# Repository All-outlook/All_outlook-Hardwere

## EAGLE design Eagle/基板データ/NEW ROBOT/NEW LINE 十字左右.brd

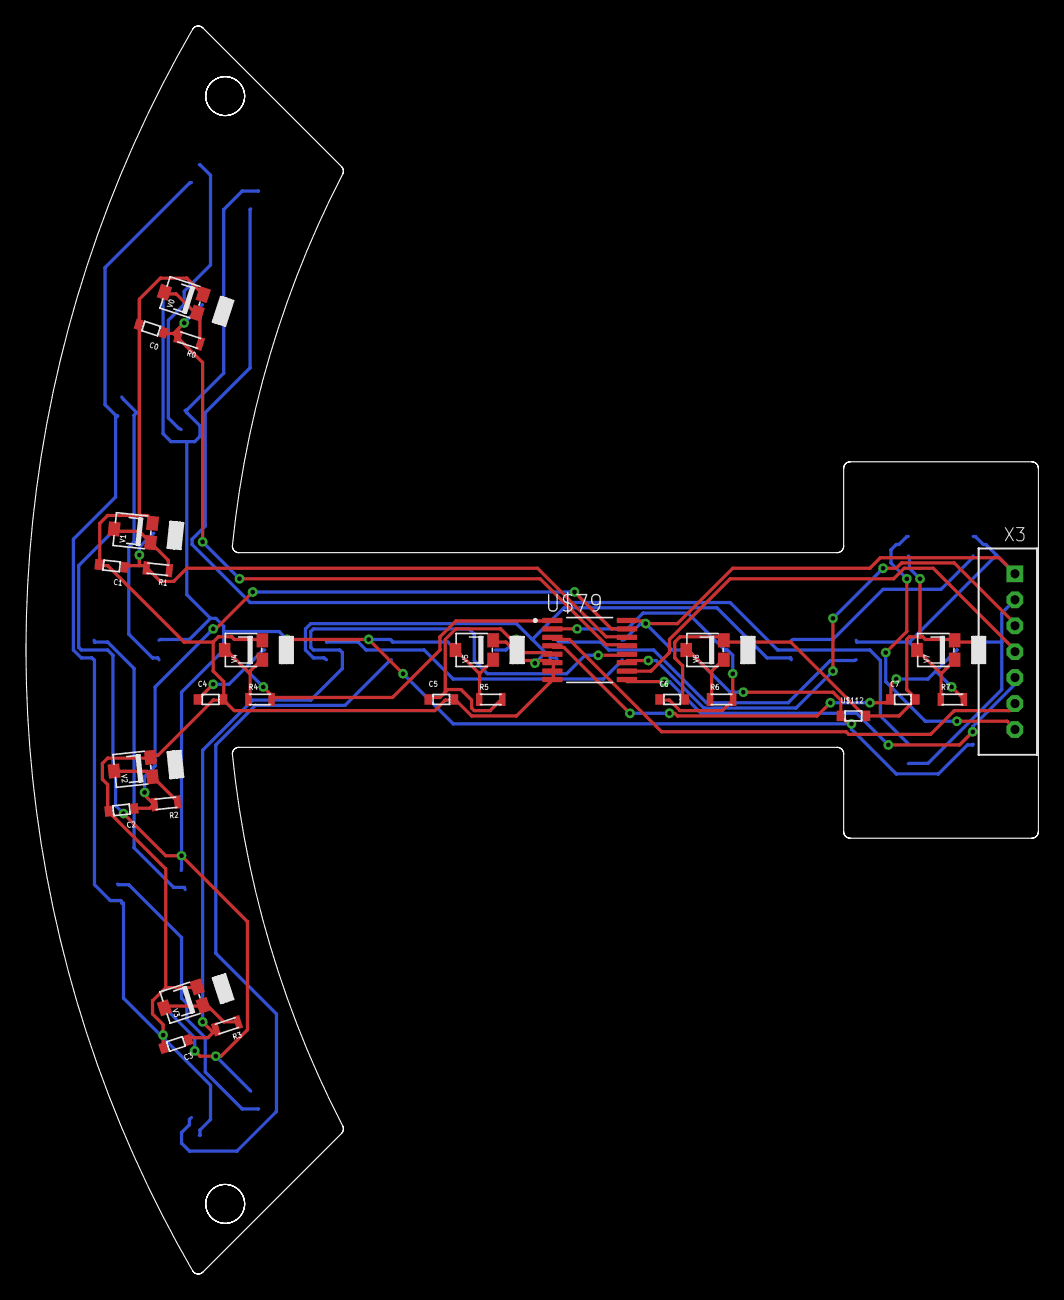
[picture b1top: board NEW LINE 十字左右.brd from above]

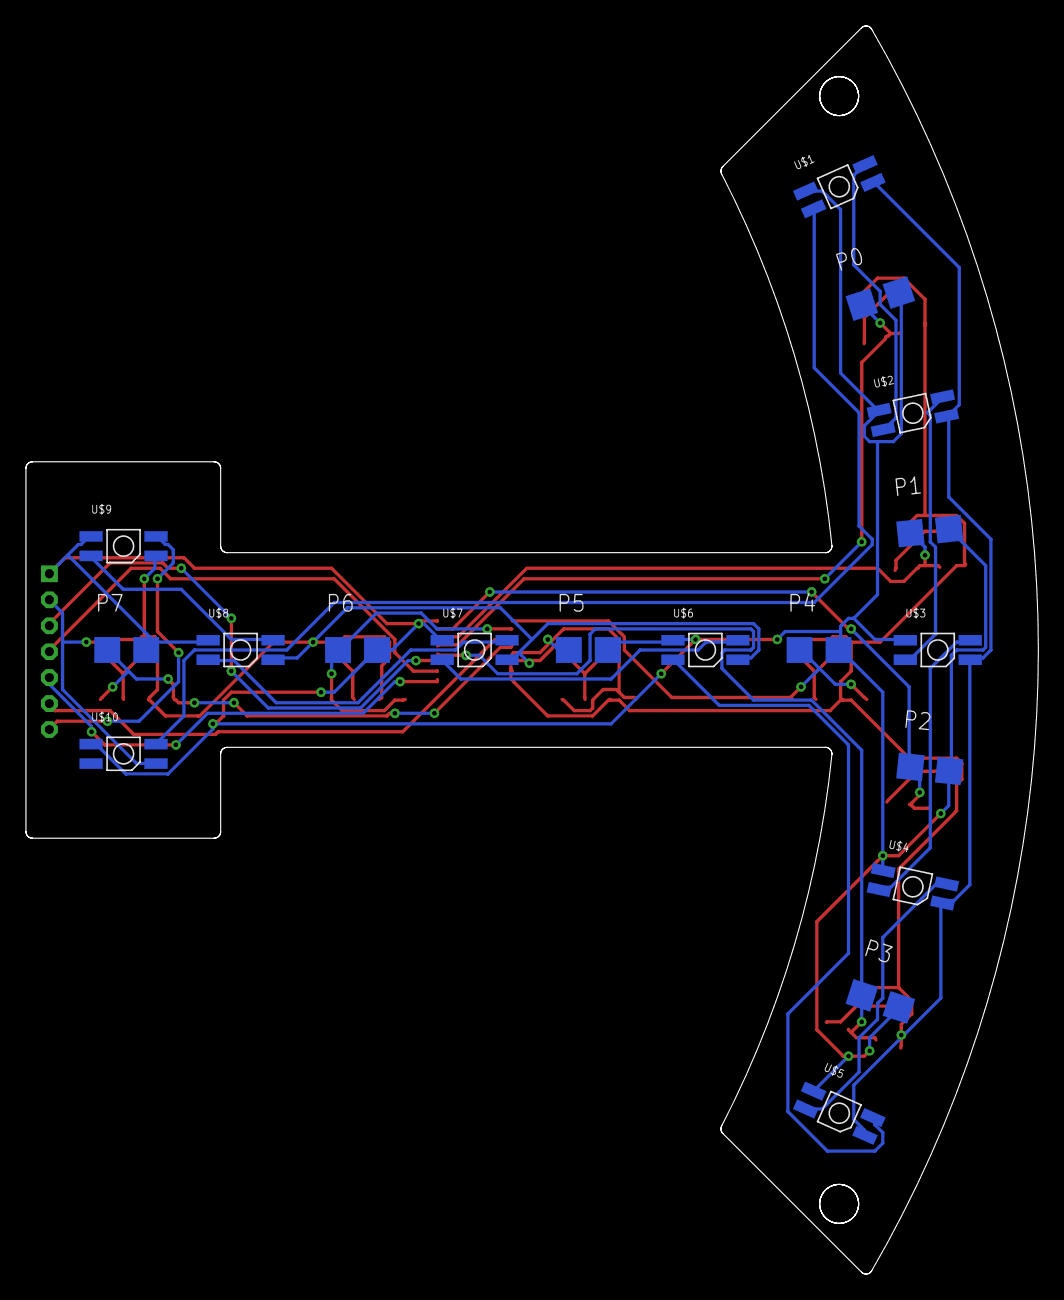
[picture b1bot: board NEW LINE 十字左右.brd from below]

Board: 2 copper layers, 78.0 x 96.2 mm, 45 parts (10 on the bottom side), 32 nets.

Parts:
C0, C1, C2, C3, C4, C5, C6, C7: 1608; CON
P0, P1, P2, P3, P4, P5, P6, P7: PHOTO
R0, R1, R2, R3, R4, R5, R6, R7: R; 1608
U$1, U$2, U$3, U$4, U$5, U$6, U$7, U$8, U$9, U$10: LED
U$79: AM; SOP65P640X120-16N
U$112: 1608; CON
V0, V1, V2, V3, V4, V5, V6, V7: VR
X3: B7B-PH-K-S

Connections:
+5V: P0.P$1, P1.P$1, P2.P$1, P3.P$1, P4.P$1, P5.P$1, P6.P$1, P7.P$1, U$1.P$1, U$2.P$1, U$3.P$1, U$4.P$1, U$5.P$1, U$6.P$1, U$7.P$1, U$8.P$1, U$9.P$1, U$10.P$1, U$79.16, U$112.P$1, X3.1
A: U$79.11, X3.3
B: U$79.10, X3.4
C: U$79.9, X3.5
CH0: C0.P$1, P0.P$2, R0.P$2, U$79.13
CH1: C1.P$1, P1.P$2, R1.P$2, U$79.14
CH2: C2.P$1, P2.P$2, R2.P$2, U$79.15
CH3: C3.P$1, P3.P$2, R3.P$2, U$79.12
CH4: C4.P$1, P4.P$2, R4.P$2, U$79.1
CH5: C5.P$1, P5.P$2, R5.P$2, U$79.5
CH6: C6.P$1, P6.P$2, R6.P$2, U$79.2
CH7: C7.P$1, P7.P$2, R7.P$2, U$79.4
COM: U$79.3, X3.6
FLED: U$9.P$4, X3.7
GND1: C0.P$2, C1.P$2, C2.P$2, C3.P$2, C4.P$2, C5.P$2, C6.P$2, C7.P$2, U$1.P$3, U$2.P$3, U$3.P$3, U$4.P$3, U$5.P$3, U$6.P$3, U$7.P$3, U$8.P$3, U$9.P$3, U$10.P$3, U$79.6, U$79.7, U$79.8, U$112.P$2, V0.P$3, V1.P$3, V2.P$3, V3.P$3, V4.P$3, V5.P$3, V6.P$3, V7.P$3, X3.2
unnamed: U$1.P$2, U$10.P$4
unnamed: U$1.P$4, U$2.P$2
unnamed: U$2.P$4, U$3.P$2
unnamed: U$3.P$4, U$4.P$2
unnamed: U$4.P$4, U$5.P$2
unnamed: U$5.P$4, U$6.P$2
unnamed: U$6.P$4, U$7.P$2
unnamed: U$7.P$4, U$8.P$2
unnamed: U$8.P$4, U$9.P$2
unnamed: R0.P$1, V0.P$1, V0.P$2
unnamed: R1.P$1, V1.P$1, V1.P$2
unnamed: R2.P$1, V2.P$1, V2.P$2
unnamed: R3.P$1, V3.P$1, V3.P$2
unnamed: R4.P$1, V4.P$1, V4.P$2
unnamed: R5.P$1, V5.P$1, V5.P$2
unnamed: R6.P$1, V6.P$1, V6.P$2
unnamed: R7.P$1, V7.P$1, V7.P$2

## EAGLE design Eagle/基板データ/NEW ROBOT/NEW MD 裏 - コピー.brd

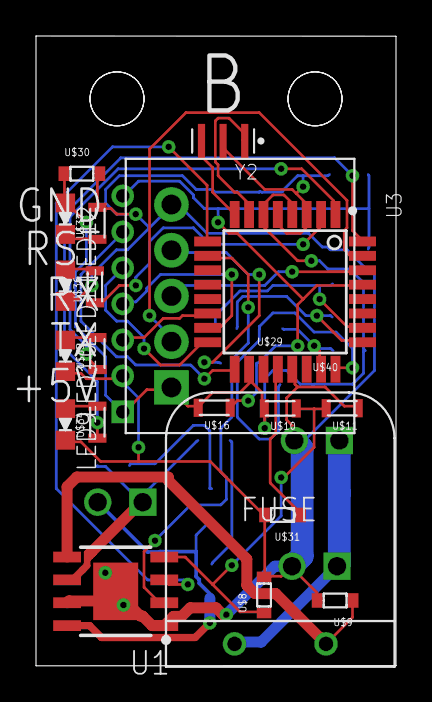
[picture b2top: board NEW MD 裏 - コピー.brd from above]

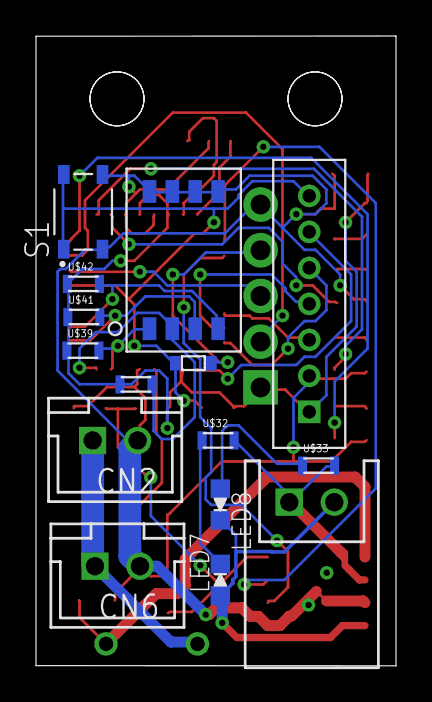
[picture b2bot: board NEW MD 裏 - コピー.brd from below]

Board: 2 copper layers, 20.0 x 35.0 mm, 35 parts (15 on the bottom side), 33 nets.

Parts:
CN2, CN6: B2B-XH-A
CN5: S2B-XH-A
LED7, LED8, LED9, LED10, LED11, LED12: LED1608
S1: SKRPACE010; SW_SKRPACE010
U1: L5973D; SOIC127P600X170-9N
U3: ATMEGA328P-AU; QFP80P900X900X120-32N
U$1: FUSE3.7A
U$8, U$9, U$29, U$30, U$31: 1608; CON
U$10, U$11, U$16, U$32, U$33, U$34, U$35, U$36, U$37, U$39, U$40, U$41, U$42: R; 1608
U$38: 4P
U$43: SPI
U$44: SI
Y2: CSTCE16M0V53-R0; OSC_CSTCE16M0V53-R0

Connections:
+5V: LED12.A, U3.4, U3.6, U3.18, U$10.P$2, U$16.P$2, U$30.P$1, U$39.P$1, U$40.P$1, U$41.P$1, U$42.P$1, U$43.P$1, U$44.P$1
A0: U3.23, U$38.1.1, U$39.P$2
A1: U3.24, U$38.2.1, U$40.P$2
A2: U3.25, U$38.3.1, U$41.P$2
A3: U3.26, U$38.4.1, U$42.P$2
D2: U3.32, U$34.P$1
D3: U3.1, U$35.P$1
D4: U3.2, U$36.P$1
GND: CN2.2, CN6.2, LED9.K, LED10.K, LED11.K, S1.3, S1.4, U1.1, U1.7, U1.9, U3.3, U3.5, U3.21, U$8.P$2, U$9.P$2, U$11.P$1, U$30.P$2, U$31.P$2, U$37.P$2, U$38.1.2, U$38.2.2, U$38.3.2, U$38.4.2, U$43.P$2, U$44.P$5, Y2.2
MISO: U3.16, U$43.P$5
MOSI: U3.15, U$43.P$4
unnamed: U1.5, U$1.P$2, U$9.P$1
unnamed: U1.4, U$8.P$1, U$10.P$1, U$11.P$2
unnamed: U3.20, U$31.P$1
unnamed: U$29.P$2, U$44.P$4
unnamed: U3.31, U$44.P$2
unnamed: U3.30, U$44.P$3
unnamed: CN2.1, CN6.1, U$1.P$1
unnamed: CN5.2, LED7.A, LED8.K, U1.8
unnamed: CN5.1, U1.6, U$32.P$2, U$33.P$2
unnamed: U1.2, U3.10
unnamed: U1.3, U3.9
unnamed: U3.7, Y2.1
unnamed: U3.8, Y2.3
unnamed: LED8.A, U$33.P$1
unnamed: LED7.K, U$32.P$1
unnamed: LED10.A, U$35.P$2
unnamed: LED9.A, U$34.P$2
unnamed: LED11.A, U$36.P$2
unnamed: LED12.K, U$37.P$1
RES: S1.1, S1.2, U3.29, U$16.P$1, U$29.P$1, U$43.P$7
SCK: U3.17, U$43.P$6
SS: U3.14, U$43.P$3

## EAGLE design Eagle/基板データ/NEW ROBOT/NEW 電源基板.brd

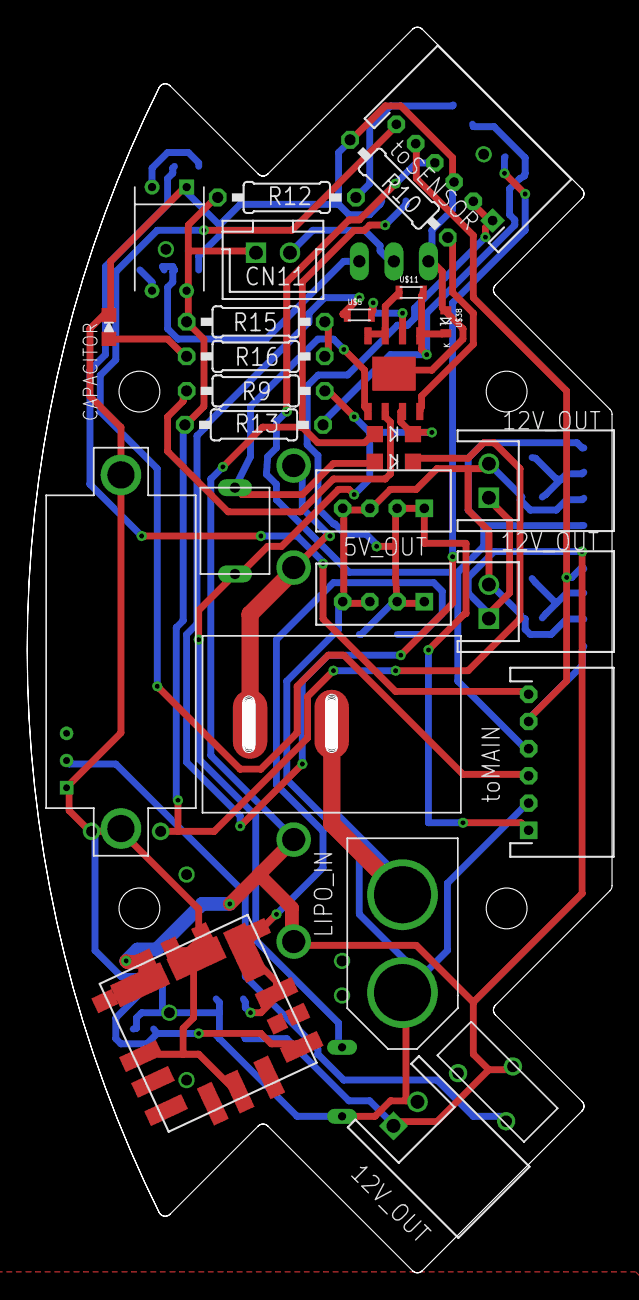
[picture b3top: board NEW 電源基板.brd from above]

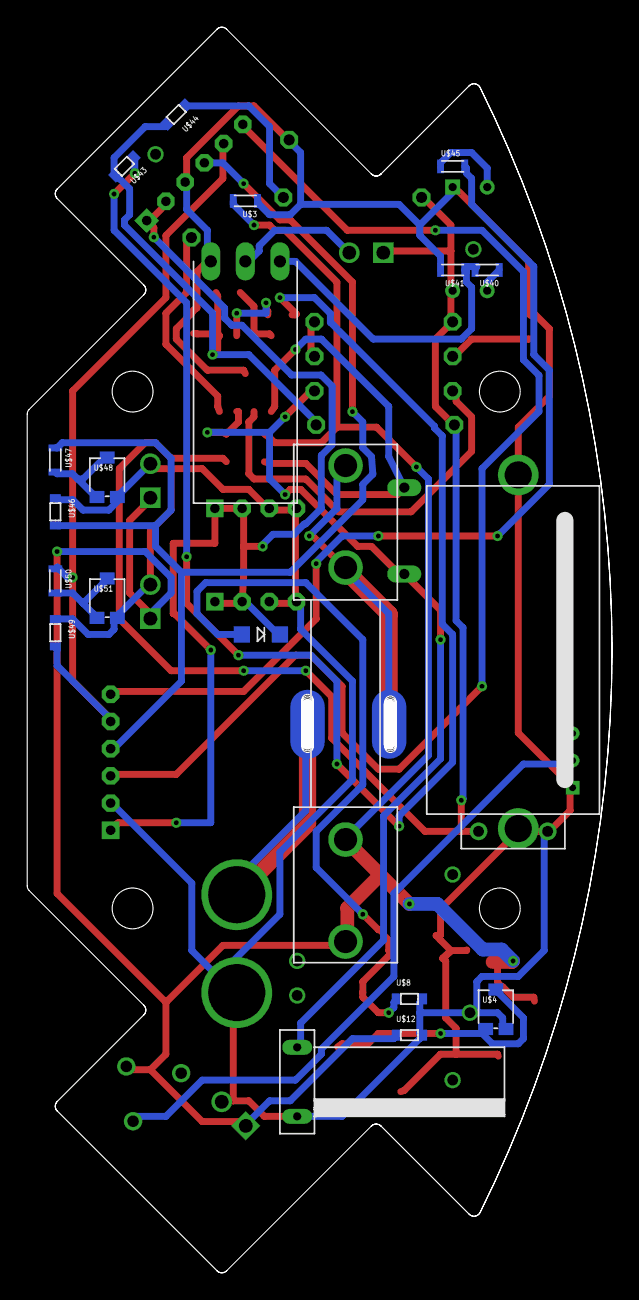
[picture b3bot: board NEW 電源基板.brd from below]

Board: 2 copper layers, 43.0 x 91.6 mm, 48 parts (20 on the bottom side), 30 nets.

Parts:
CAPACITOR: LED1608
CN5, CN6, CN7: S2B-XH-A
CN11: B2B-XH-A
FUES1: FUSE
R9, R10, R12, R13, R15, R16: 0207/10
U1: L5973D; HSOP8
U$1: SW3
U$2: DCDC; DC-DC
U$3, U$5, U$11, U$40, U$41, U$45, U$47, U$50: R; 1608
U$4, U$48, U$51: VR
U$6: V
U$7: XT60
U$8, U$12, U$43, U$44, U$46, U$49: 1608; CON
U$9: SSW
U$10, U$32, U$33: D
U$13: I
U$36: MOS
U$37: PHOTOCOUPLER
U$38: TD
U$39: FGFG2; FG2
U$42: 10
X1, X2: B4B-PH-K-S
X5, X6: S6B-PH-K-S

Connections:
+5V: U$10.P$2, X1.1, X1.2, X2.1, X2.2, X5.1, X5.2, X6.1
+12V: CN5.1, CN6.1, CN7.1, FUES1.P$1, FUES1.P$2, U$2.P$9, U$2.P$14, U$2.P$15, U$3.P$2, U$9.P$3, U$12.P$1, U$32.P$1
B1: U$46.P$2, U$47.P$1, X5.4, X6.4
B2: U$49.P$2, U$50.P$1, X5.5, X6.5
FLED: X5.6, X6.3
GND: CAPACITOR.K, CN5.2, CN6.2, CN7.2, R10.1, U1.9, U$2.P$1, U$2.P$5, U$2.P$10, U$2.P$16, U$2.P$17, U$3.P$1, U$4.P$3, U$6.P$1, U$6.P$4, U$6.P$5, U$7.P$2, U$8.P$2, U$12.P$2, U$36.P$3, U$37.P$1, U$38.P$1, U$39.P$2, U$41.P$2, U$42.P$2, U$46.P$1, U$48.P$3, U$49.P$1, U$51.P$3, X1.3, X1.4, X2.3, X2.4, X5.3, X6.2
K: U$45.P$2, X6.6
unnamed: U$6.P$2, U$9.P$1
unnamed: U$2.P$7, U$4.P$1, U$4.P$2
unnamed: U$2.P$8, U$2.P$11, U$2.P$18, U$8.P$1, U$10.P$1
unnamed: FUES1.P$3, FUES1.P$4, U$1.P$2, U$1.P$4
unnamed: U$1.P$1, U$1.P$3, U$7.P$1
unnamed: CN11.1, R12.1, R13.1, R15.1, U$33.P$2, U$37.P$4, U$39.P$1
unnamed: U$37.P$3, U$40.P$1
unnamed: CN11.2, U$36.P$2
unnamed: U$36.P$1, U$40.P$2, U$41.P$1
unnamed: R9.2, U1.3, U$13.P$1, U$32.P$2, U$42.P$1
unnamed: R9.1, U1.2
unnamed: R10.2, U1.4
unnamed: R13.2, U1.5, U$11.P$2, U$38.P$2, U$43.P$2, U$44.P$2
unnamed: R12.2, U$44.P$1
unnamed: U1.6, U$5.P$2
unnamed: U$5.P$1, U$43.P$1
unnamed: U$37.P$2, U$45.P$1
unnamed: U$47.P$2, U$48.P$1, U$48.P$2
unnamed: U$50.P$2, U$51.P$1, U$51.P$2
unnamed: R15.2, R16.1
unnamed: CAPACITOR.A, R16.2
PGND: U1.7, U1.8, U$11.P$1
SW: U1.1, U$13.P$2, U$33.P$1

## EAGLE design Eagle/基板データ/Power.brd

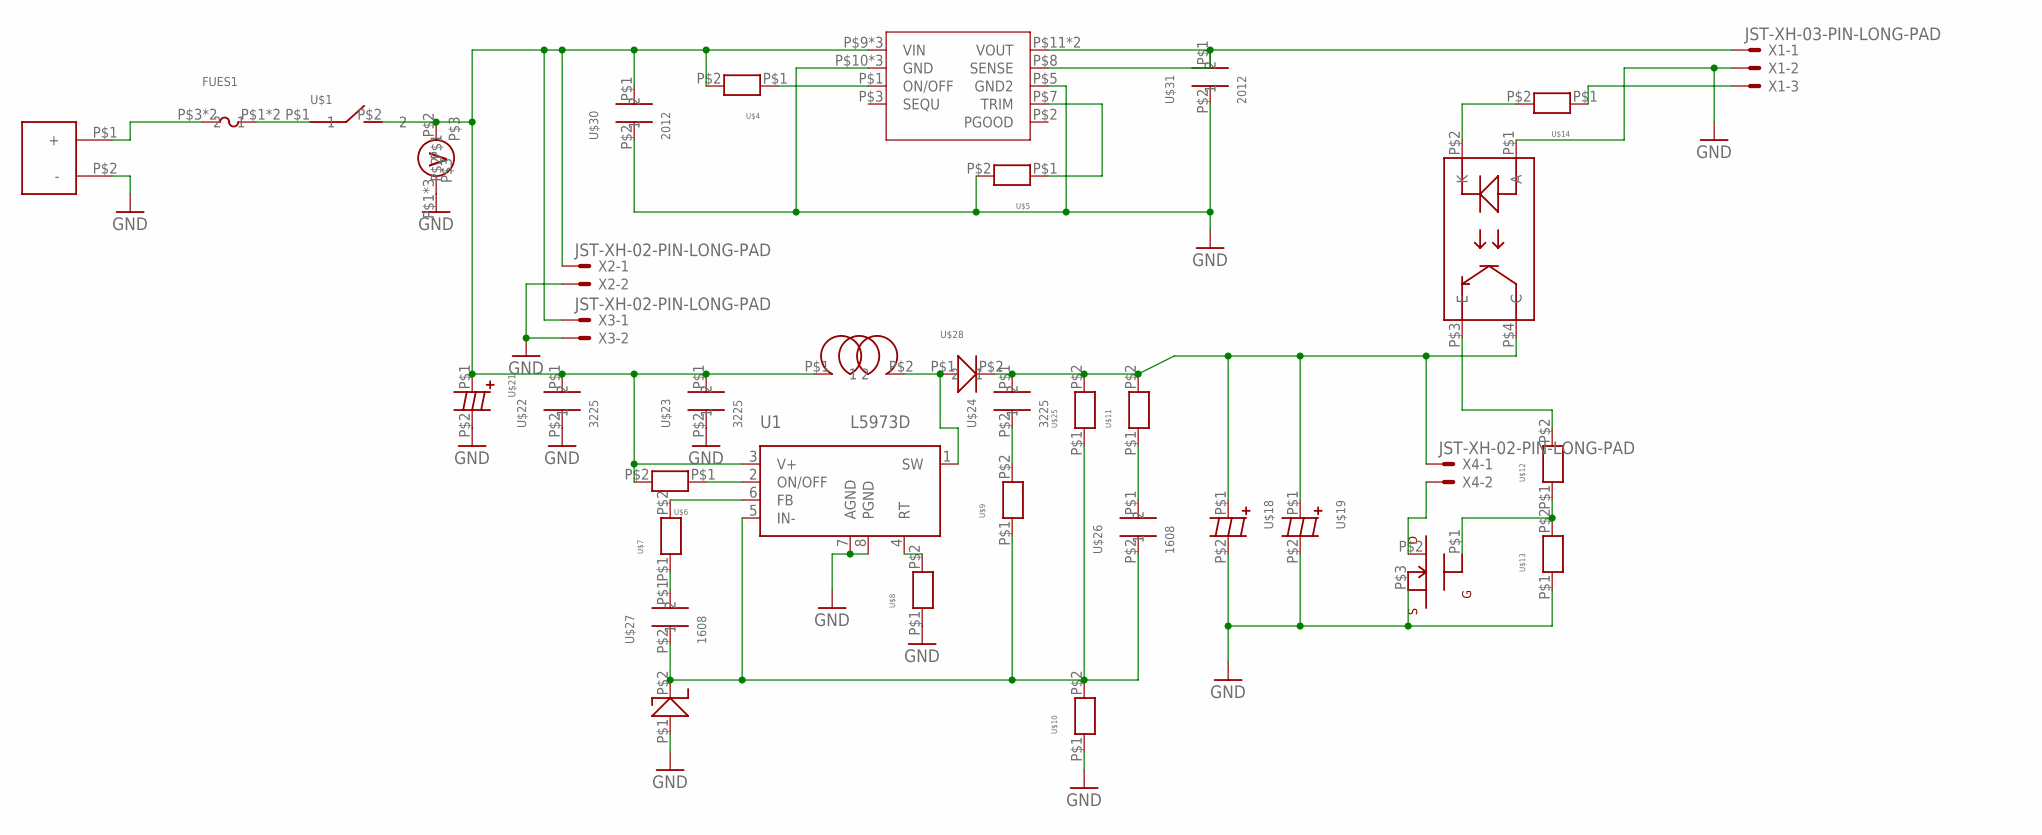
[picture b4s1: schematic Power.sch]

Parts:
FUES1: FUSE
U1: L5973D; HSOP8
U$1: SW
U$2: V
U$3: DCDC; DC-DC
U$4, U$5, U$6, U$7, U$8, U$9, U$10, U$11, U$12, U$13, U$14, U$25: R; 1608
U$15: PHOTOCOUPLER
U$16: XT60
U$17: MOS
U$18, U$19, U$21: C
U$20: I
U$22, U$23, U$24: 3225
U$26, U$27: 1608; CON
U$28: D
U$29: TD
U$30, U$31: 2012
X1: JST-XH-03-PIN-LONG-PAD; JST-XH-03-PACKAGE-LONG-PAD
X2, X3, X4: JST-XH-02-PIN-LONG-PAD; JST-XH-02-PACKAGE-LONG-PAD

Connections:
GND: U1.7 (AGND), U1.8 (PGND), U1.9 (GND), U$2.P$1, U$2.P$4, U$2.P$5, U$3.P$5 (GND2), U$3.P$10 (GND), U$3.P$16 (GND), U$3.P$17 (GND), U$5.P$2, U$8.P$1, U$10.P$1, U$13.P$1, U$15.P$1 (A), U$16.P$2 (-), U$17.P$3, U$18.P$2, U$19.P$2, U$21.P$2, U$22.P$2 (2), U$23.P$2 (2), U$29.P$1, U$30.P$2 (2), U$31.P$2 (2), X1.2, X2.2, X3.2
unnamed: FUES1.P$1 (2), FUES1.P$2 (2), U$1.P$1 (1)
unnamed: FUES1.P$3 (1), FUES1.P$4 (1), U$16.P$1 (+)
unnamed: U$17.P$2, X4.2
unnamed: U$12.P$1, U$13.P$2, U$17.P$1
unnamed: U$12.P$2, U$15.P$3 (E)
unnamed: U$11.P$1, U$26.P$1 (1)
unnamed: U$3.P$8 (SENSE), U$3.P$11 (VOUT), U$3.P$18 (VOUT), U$31.P$1 (1), X1.1
unnamed: U$14.P$2, U$15.P$2 (K)
unnamed: U$3.P$1 (ON/OFF), U$4.P$1
unnamed: U1.2 (ON/OFF), U$6.P$1
unnamed: U1.6 (FB), U$7.P$2
unnamed: U$7.P$1, U$27.P$1 (1)
unnamed: U$3.P$7 (TRIM), U$5.P$1
unnamed: U$11.P$2, U$15.P$4 (C), U$18.P$1, U$19.P$1, U$24.P$1 (1), U$25.P$2, U$28.P$2 (2), X4.1
unnamed: U$9.P$2, U$24.P$2 (2)
unnamed: U1.5 (IN-), U$9.P$1, U$10.P$2, U$25.P$1, U$26.P$2 (2), U$27.P$2 (2), U$29.P$2
unnamed: U1.4 (RT), U$8.P$2
unnamed: U1.3 (V+), U$1.P$2 (2), U$2.P$2, U$3.P$9 (VIN), U$3.P$14 (VIN), U$3.P$15 (VIN), U$4.P$2, U$6.P$2, U$20.P$1 (1), U$21.P$1, U$22.P$1 (1), U$23.P$1 (1), U$30.P$1 (1), X2.1, X3.1
unnamed: U$14.P$1, X1.3
SW: U1.1 (SW), U$20.P$2 (2), U$28.P$1 (1)

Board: 2 copper layers, 37 parts (0 on the bottom side), 21 nets, no tracks yet.

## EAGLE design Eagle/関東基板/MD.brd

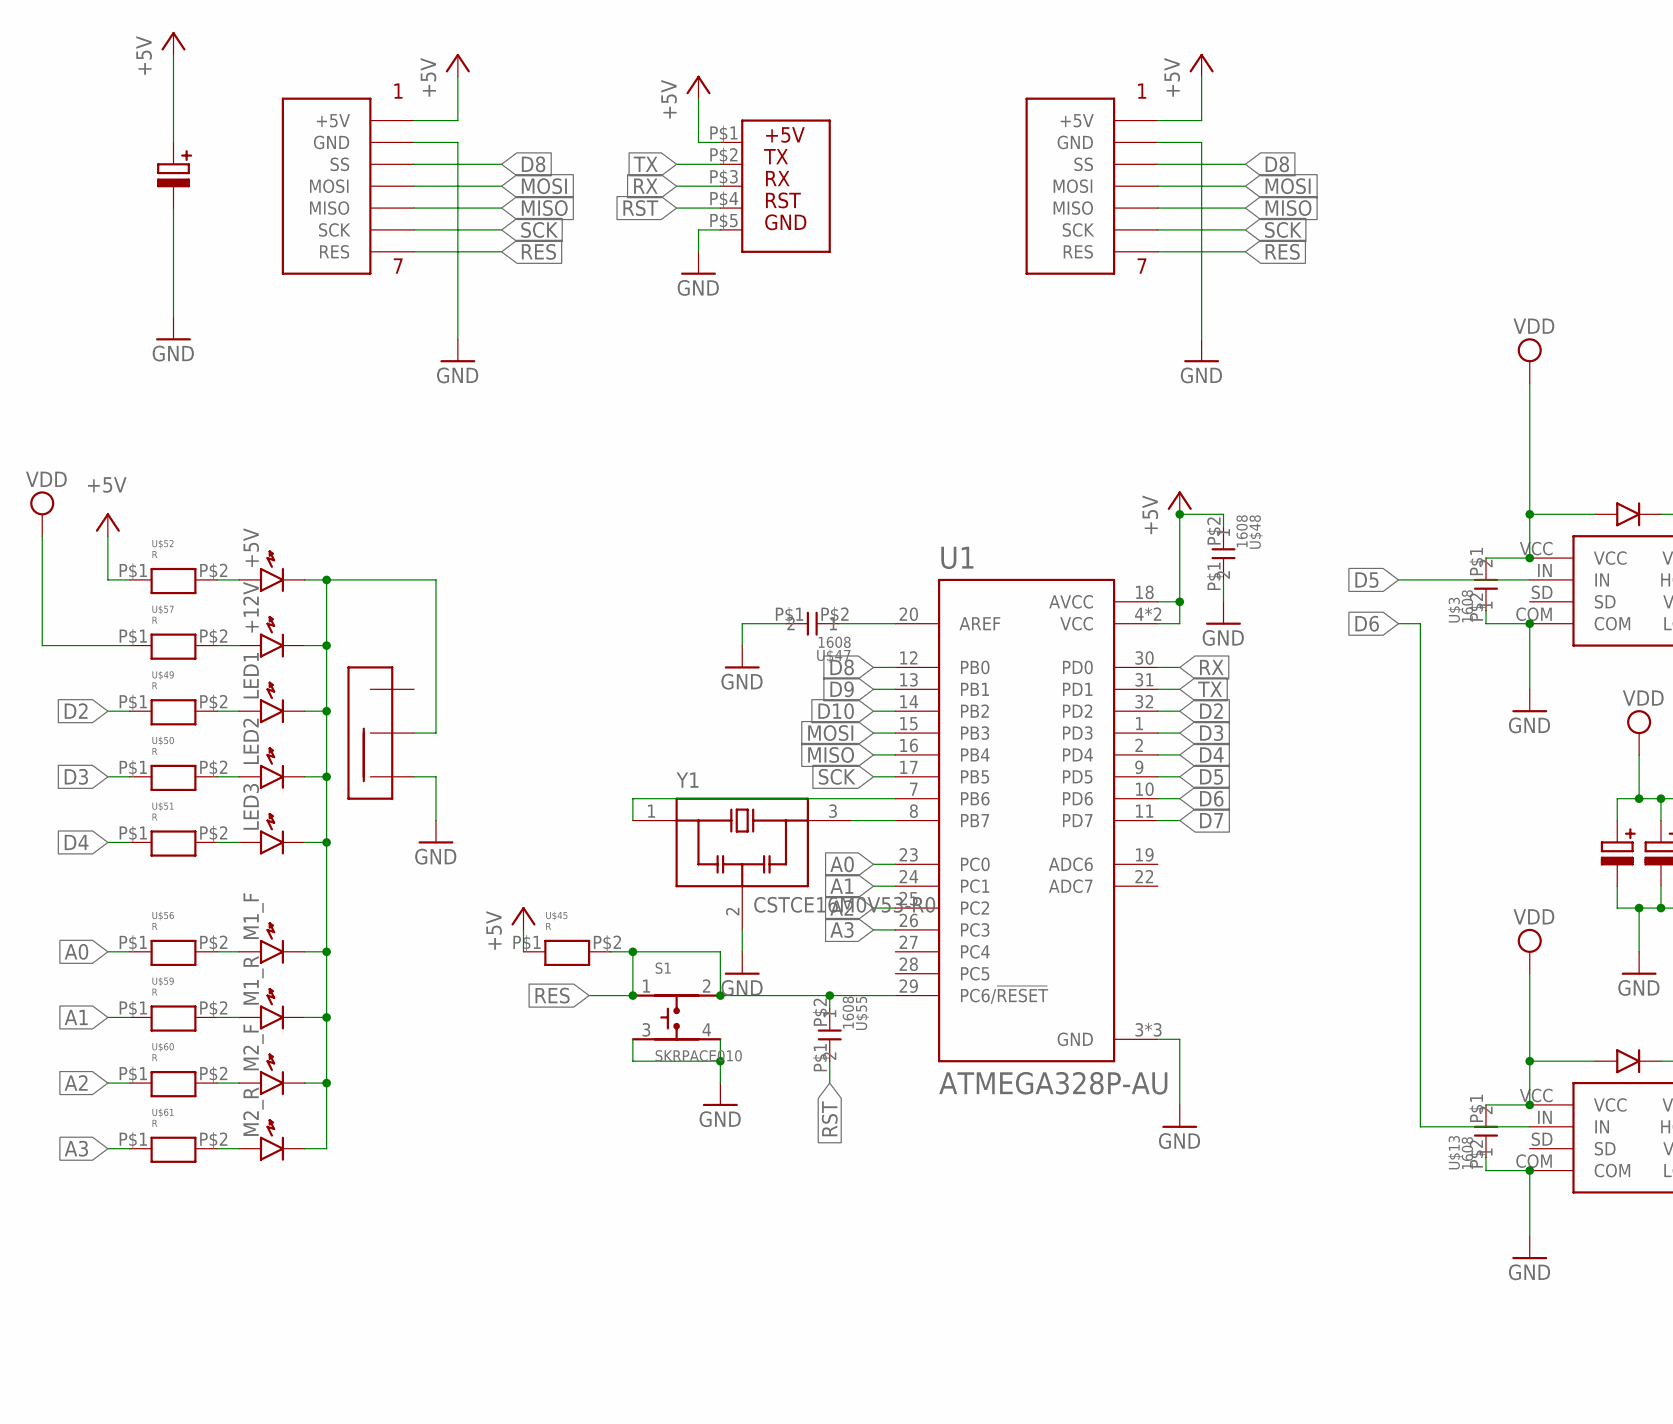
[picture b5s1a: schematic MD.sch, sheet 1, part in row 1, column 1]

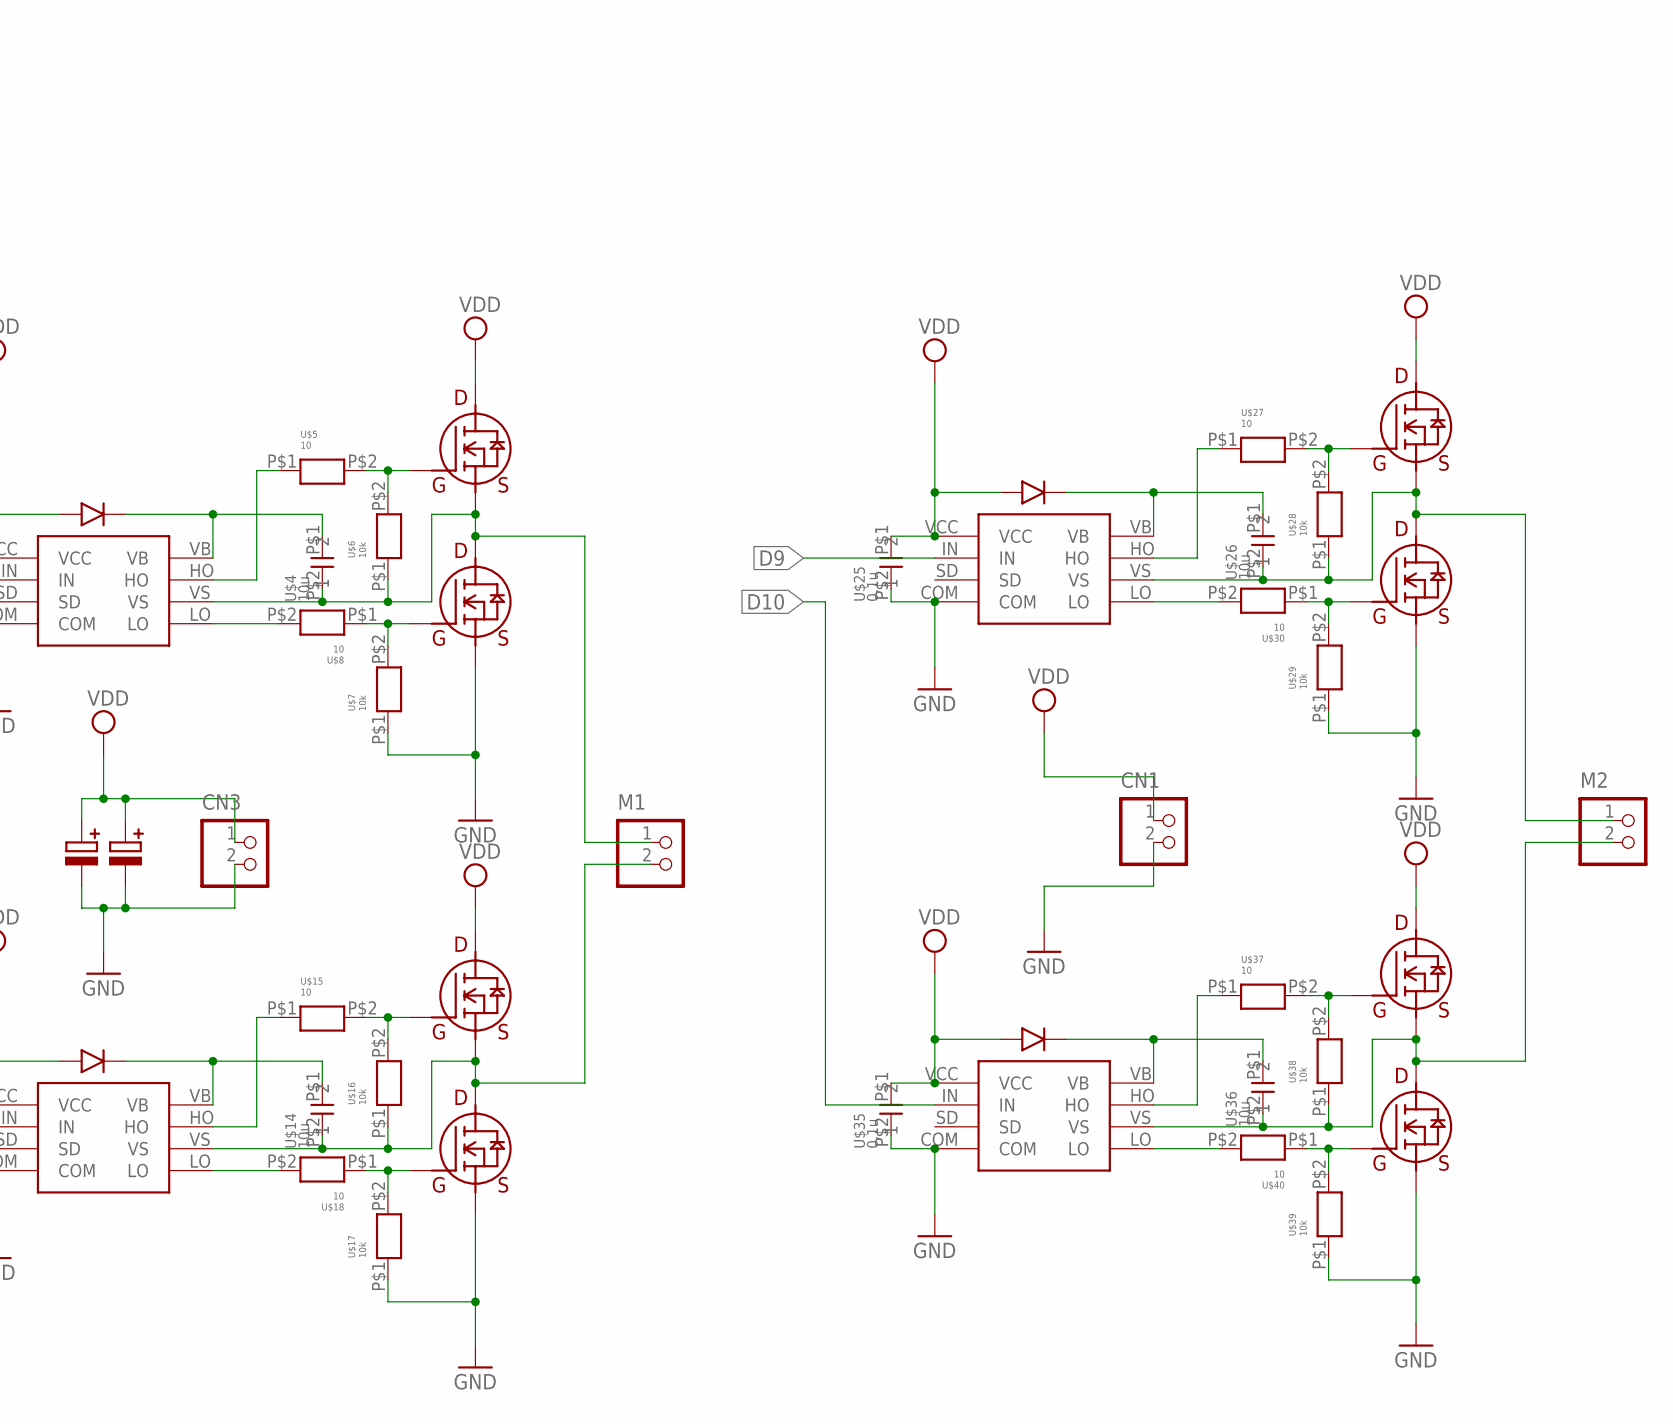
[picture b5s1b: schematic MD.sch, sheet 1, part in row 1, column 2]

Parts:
+5V, +12V: LED1608
CN1, CN3: B2B-XH-A
LED1, LED2, LED3: LED1608
M1, M2: S2B-XH-A
M1_F, M1_R, M2_F, M2_R: LED1608
S1: SKRPACE010; SW_SKRPACE010
U1: ATMEGA328P-AU; QFP80P900X900X120-32N
U$1, U$11, U$23, U$33: IR2302
U$2, U$12, U$24, U$34: 1N4148
U$3, U$13, U$47, U$48, U$55: 1608; CON
U$4, U$14, U$26, U$36: 10u; CON
U$5, U$8, U$15, U$18, U$27, U$30, U$37, U$40: 10; 1608
U$6, U$7, U$16, U$17, U$28, U$29, U$38, U$39: 10k; 1608
U$9, U$10, U$19, U$20, U$31, U$32, U$41, U$42: TK8S06K3L
U$21, U$22, U$58: 25V100
U$25, U$35: 0.1u; CON
U$45, U$49, U$50, U$51, U$52, U$56, U$57, U$59, U$60, U$61: R; 1608
U$46, U$62: SPI
U$53: SSW
U$54: SI
Y1: CSTCE16M0V53-R0; OSC_CSTCE16M0V53-R0

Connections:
+5V: U1.4 (VCC), U1.6 (VCC), U1.18 (AVCC), U$45.P$1, U$46.P$1 (+5V), U$48.P$2 (2), U$52.P$1, U$54.P$1, U$58.P$1, U$62.P$1 (+5V)
A0: U1.23 (PC0), U$56.P$1
A1: U1.24 (PC1), U$59.P$1
A2: U1.25 (PC2), U$60.P$1
A3: U1.26 (PC3), U$61.P$1
D2: U1.32 (PD2), U$49.P$1
D3: U1.1 (PD3), U$50.P$1
D4: U1.2 (PD4), U$51.P$1
D5: U1.9 (PD5), U$1.IN
D6: U1.10 (PD6), U$11.IN
D7: U1.11 (PD7)
D8: U1.12 (PB0), U$46.P$3 (SS), U$62.P$3 (SS)
D9: U1.13 (PB1), U$23.IN
D10: U1.14 (PB2), U$33.IN
GND: CN1.2, CN3.2, S1.3, S1.4, U1.3 (GND), U1.5 (GND), U1.21 (GND), U$1.COM, U$3.P$2 (2), U$7.P$1, U$10.S, U$11.COM, U$13.P$2 (2), U$17.P$1, U$20.S, U$21.P$2, U$22.P$2, U$23.COM, U$25.P$2 (2), U$29.P$1, U$32.S, U$33.COM, U$35.P$2 (2), U$39.P$1, U$42.S, U$46.P$2 (GND), U$47.P$1 (1), U$48.P$1 (1), U$53.P$1, U$54.P$5, U$58.P$2, U$62.P$2 (GND), Y1.2 (GND)
MISO: U1.16 (PB4), U$46.P$5 (MISO), U$62.P$5 (MISO)
MOSI: U1.15 (PB3), U$46.P$4 (MOSI), U$62.P$4 (MOSI)
unnamed: U$23.VB, U$24.P$2, U$26.P$1 (1)
unnamed: M2.1, U$23.VS, U$26.P$2 (2), U$28.P$1, U$31.S, U$32.D
unnamed: U$1.VB, U$2.P$2, U$4.P$1 (1)
unnamed: M1.1, U$1.VS, U$4.P$2 (2), U$6.P$1, U$9.S, U$10.D
unnamed: LED1.A, U$49.P$2
unnamed: U$5.P$2, U$6.P$2, U$9.G
unnamed: U$1.HO, U$5.P$1
unnamed: U$1.LO, U$8.P$2
unnamed: U$7.P$2, U$8.P$1, U$10.G
unnamed: U$27.P$2, U$28.P$2, U$31.G
unnamed: U$23.HO, U$27.P$1
unnamed: U$11.VB, U$12.P$2, U$14.P$1 (1)
unnamed: M1.2, U$11.VS, U$14.P$2 (2), U$16.P$1, U$19.S, U$20.D
unnamed: U$15.P$2, U$16.P$2, U$19.G
unnamed: U$11.HO, U$15.P$1
unnamed: U$11.LO, U$18.P$2
unnamed: U$17.P$2, U$18.P$1, U$20.G
unnamed: LED2.A, U$50.P$2
unnamed: U$23.LO, U$30.P$2
unnamed: U$29.P$2, U$30.P$1, U$32.G
unnamed: LED3.A, U$51.P$2
unnamed: U$33.VB, U$34.P$2, U$36.P$1 (1)
unnamed: M2.2, U$33.VS, U$36.P$2 (2), U$38.P$1, U$41.S, U$42.D
unnamed: U$37.P$2, U$38.P$2, U$41.G
unnamed: U$33.HO, U$37.P$1
unnamed: U$33.LO, U$40.P$2
unnamed: U$39.P$2, U$40.P$1, U$42.G
unnamed: +5V.A, U$52.P$2
unnamed: +5V.K, +12V.K, LED1.K, LED2.K, LED3.K, M1_F.K, M1_R.K, M2_F.K, M2_R.K, U$53.P$3
unnamed: +12V.A, U$57.P$2
unnamed: M1_R.A, U$59.P$2
unnamed: M1_F.A, U$56.P$2
unnamed: M2_R.A, U$61.P$2
unnamed: M2_F.A, U$60.P$2
unnamed: U1.8 (PB7), Y1.3 (OUT)
unnamed: U1.7 (PB6), Y1.1 (IN)
unnamed: U1.20 (AREF), U$47.P$2 (2)
RES: S1.1, S1.2, U1.29 (PC6/!RESET), U$45.P$2, U$46.P$7 (RES), U$55.P$2 (2), U$62.P$7 (RES)
RST: U$54.P$4, U$55.P$1 (1)
RX: U1.30 (PD0), U$54.P$3
SCK: U1.17 (PB5), U$46.P$6 (SCK), U$62.P$6 (SCK)
TX: U1.31 (PD1), U$54.P$2
VDD: CN1.1, CN3.1, U$1.VCC, U$2.P$1, U$3.P$1 (1), U$9.D, U$11.VCC, U$12.P$1, U$13.P$1 (1), U$19.D, U$21.P$1, U$22.P$1, U$23.VCC, U$24.P$1, U$25.P$1 (1), U$31.D, U$33.VCC, U$34.P$1, U$35.P$1 (1), U$41.D, U$57.P$1

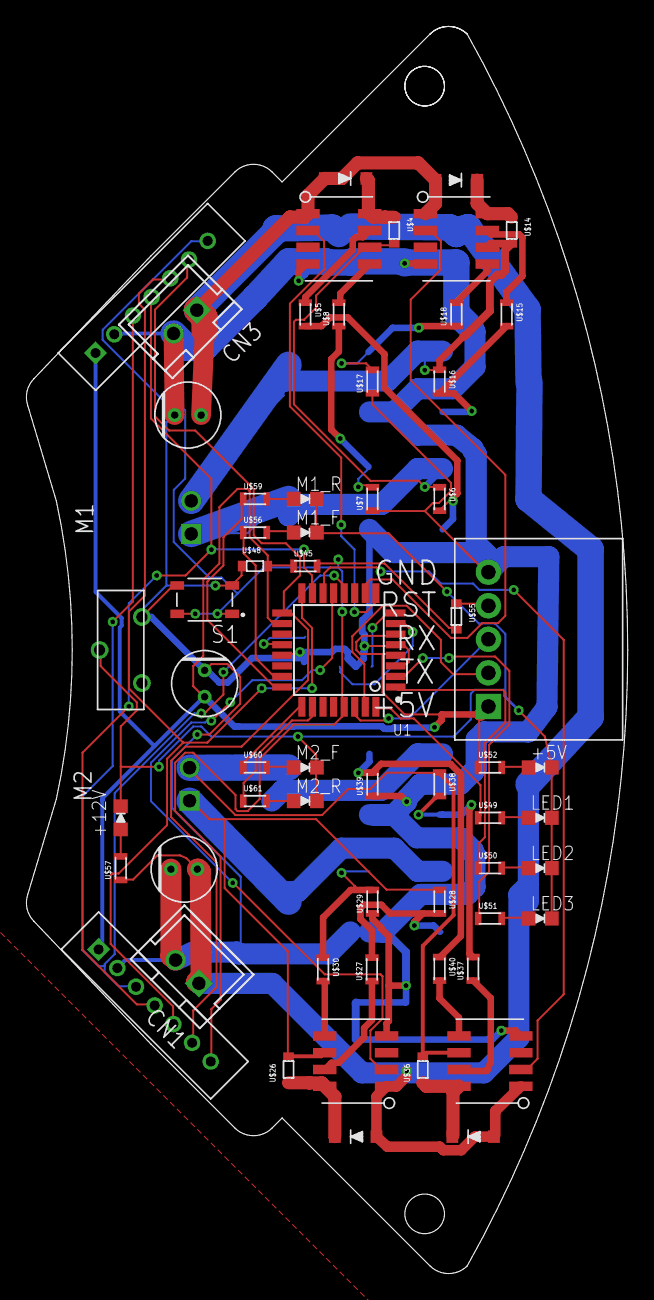
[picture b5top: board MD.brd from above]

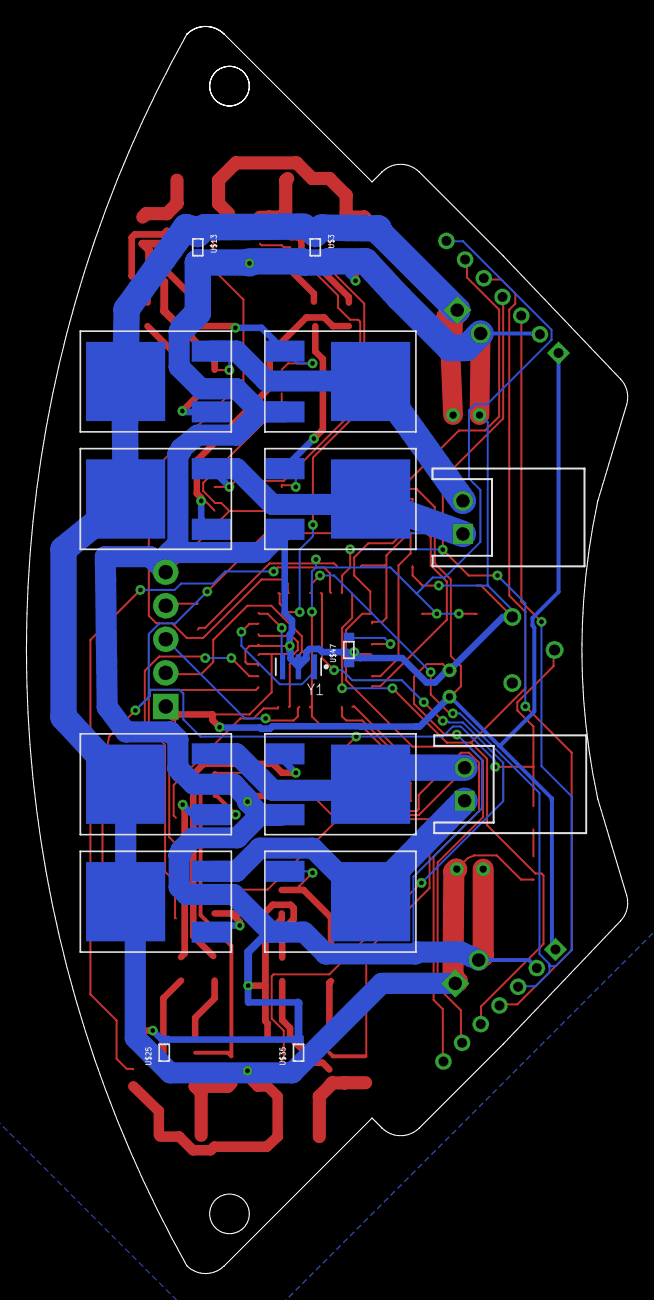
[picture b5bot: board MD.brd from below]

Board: 2 copper layers, 45.5 x 94.4 mm, 76 parts (16 on the bottom side), 59 nets.

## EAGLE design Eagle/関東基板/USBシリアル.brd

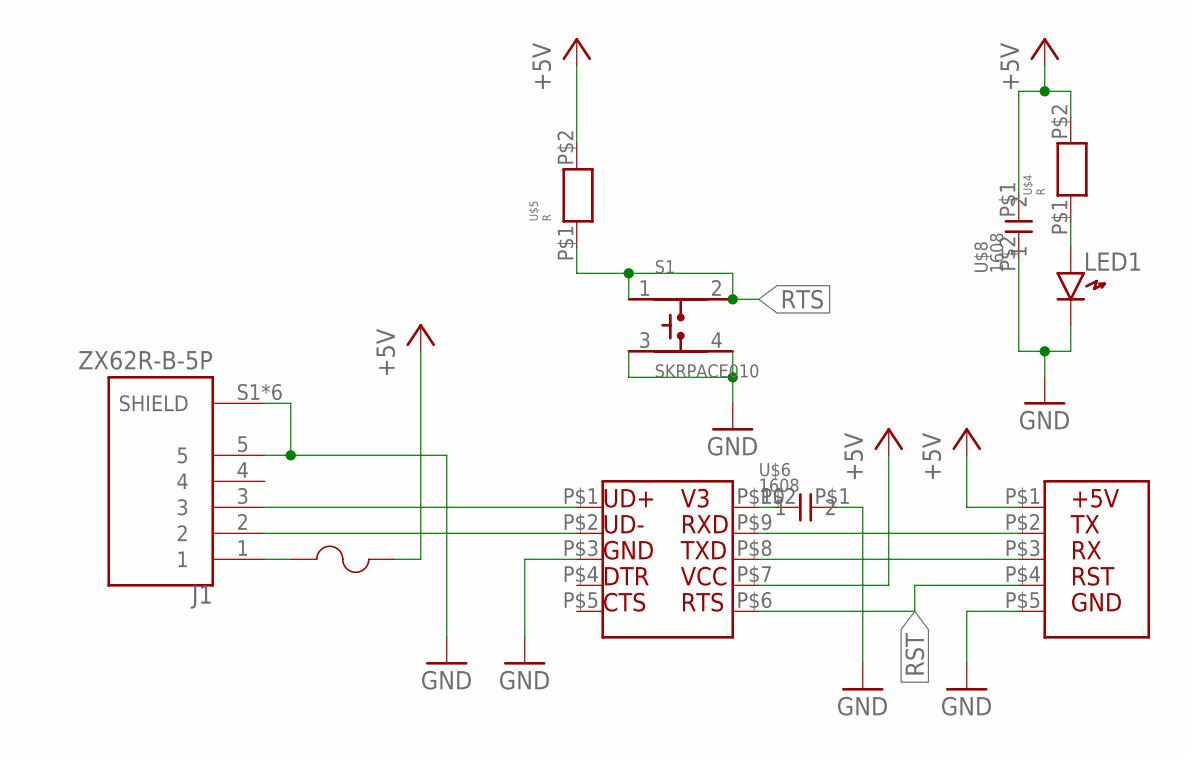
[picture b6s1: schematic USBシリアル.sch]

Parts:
J1: ZX62R-B-5P; HRS_ZX62R-B-5P
LED1: LED1608
S1: SKRPACE010; SW_SKRPACE010
U$1: CH340K
U$2: F
U$3: SI
U$4, U$5: R; 1608
U$6, U$8: 1608; CON

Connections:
+5V: U$1.P$7, U$2.P$1, U$3.P$1, U$4.P$2, U$5.P$2, U$8.P$1 (1)
GND: J1.5, J1.S1 (SHIELD), J1.S2 (SHIELD), J1.S3 (SHIELD), J1.S4 (SHIELD), J1.S5 (SHIELD), J1.S6 (SHIELD), LED1.K, S1.3, S1.4, U$1.P$3, U$3.P$5, U$6.P$1 (1), U$8.P$2 (2)
unnamed: J1.2, U$1.P$2
unnamed: J1.3, U$1.P$1
unnamed: LED1.A, U$4.P$1
unnamed: J1.1, U$2.P$2
unnamed: U$1.P$8, U$3.P$3
unnamed: U$1.P$9, U$3.P$2
unnamed: U$1.P$10, U$6.P$2 (2)
RST: U$1.P$6, U$3.P$4
RTS: S1.1, S1.2, U$5.P$1

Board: 2 copper layers, 10 parts (0 on the bottom side), 11 nets, no tracks yet.

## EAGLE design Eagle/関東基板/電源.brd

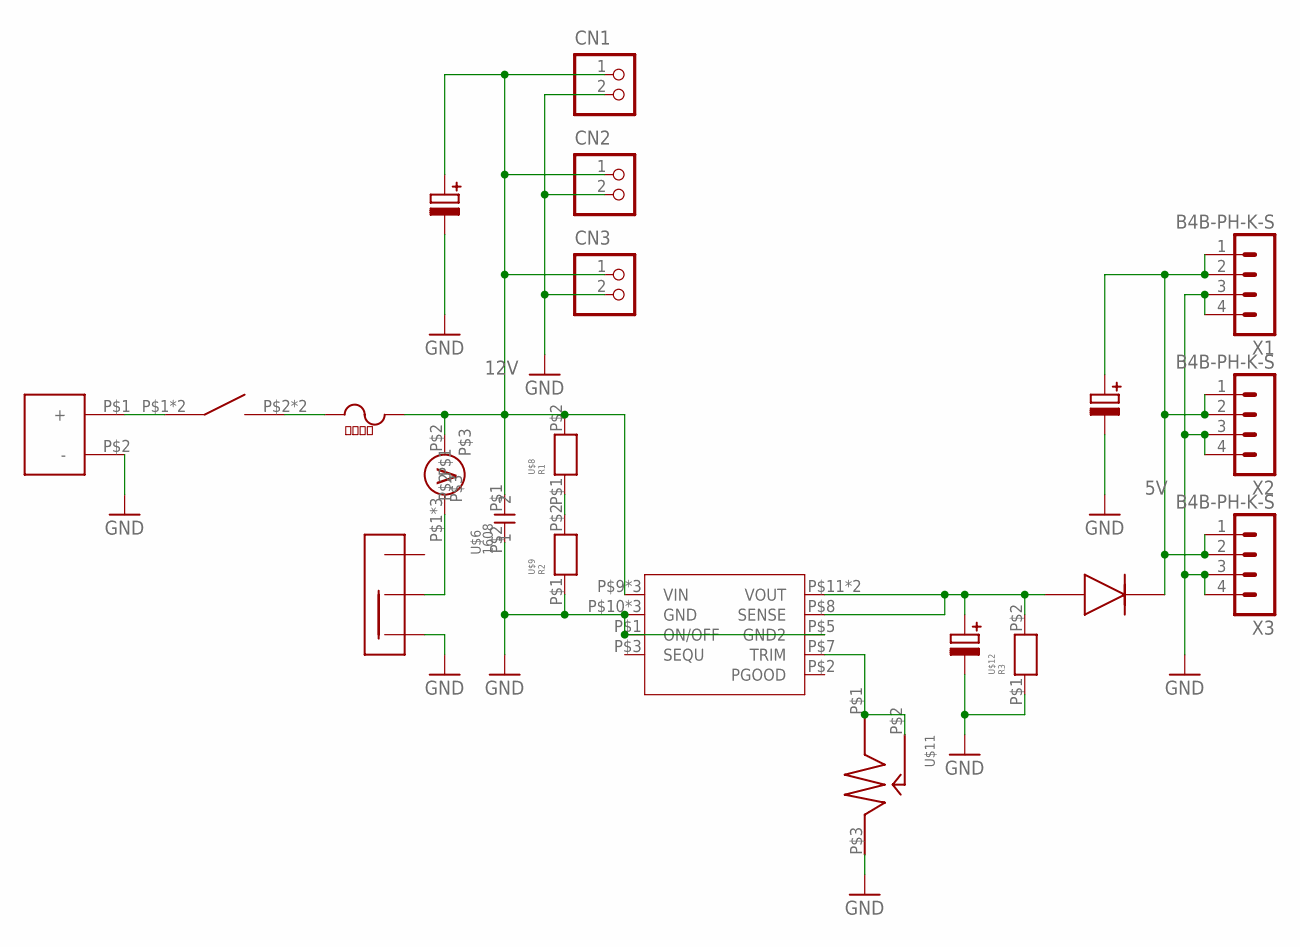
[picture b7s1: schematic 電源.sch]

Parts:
CN1, CN2, CN3: S2B-XH-A
U$1: XT60
U$2: MF; ｍｆ
U$3: V
U$4: SW3
U$5: DCDC; DC-DC
U$6: 1608; CON
U$7, U$15, U$19: 25V100
U$8: R1; 1608
U$9: R2; 1608
U$10: 40V5A
U$11: VR
U$12: R3; 1608
U$16: SSW
X1, X2, X3: B4B-PH-K-S

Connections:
5V: U$10.P$2, U$19.P$1, X1.1, X1.2, X2.1, X2.2, X3.1, X3.2
12V: CN1.1, CN2.1, CN3.1, U$2.P$3, U$2.P$4, U$3.P$2, U$5.P$9 (VIN), U$5.P$14 (VIN), U$5.P$15 (VIN), U$6.P$1 (1), U$8.P$2, U$15.P$1
GND: CN1.2, CN2.2, CN3.2, U$1.P$2 (-), U$5.P$1 (ON/OFF), U$5.P$5 (GND2), U$5.P$10 (GND), U$5.P$16 (GND), U$5.P$17 (GND), U$6.P$2 (2), U$7.P$2, U$9.P$1, U$11.P$3, U$12.P$1, U$15.P$2, U$16.P$1, U$19.P$2, X1.3, X1.4, X2.3, X2.4, X3.3, X3.4
unnamed: U$1.P$1 (+), U$4.P$1, U$4.P$3
unnamed: U$2.P$1, U$2.P$2, U$4.P$2, U$4.P$4
unnamed: U$5.P$8 (SENSE), U$5.P$11 (VOUT), U$5.P$18 (VOUT), U$7.P$1, U$10.P$1, U$12.P$2
unnamed: U$8.P$1, U$9.P$2
unnamed: U$5.P$7 (TRIM), U$11.P$1, U$11.P$2
unnamed: U$3.P$1, U$3.P$4, U$3.P$5, U$16.P$3
